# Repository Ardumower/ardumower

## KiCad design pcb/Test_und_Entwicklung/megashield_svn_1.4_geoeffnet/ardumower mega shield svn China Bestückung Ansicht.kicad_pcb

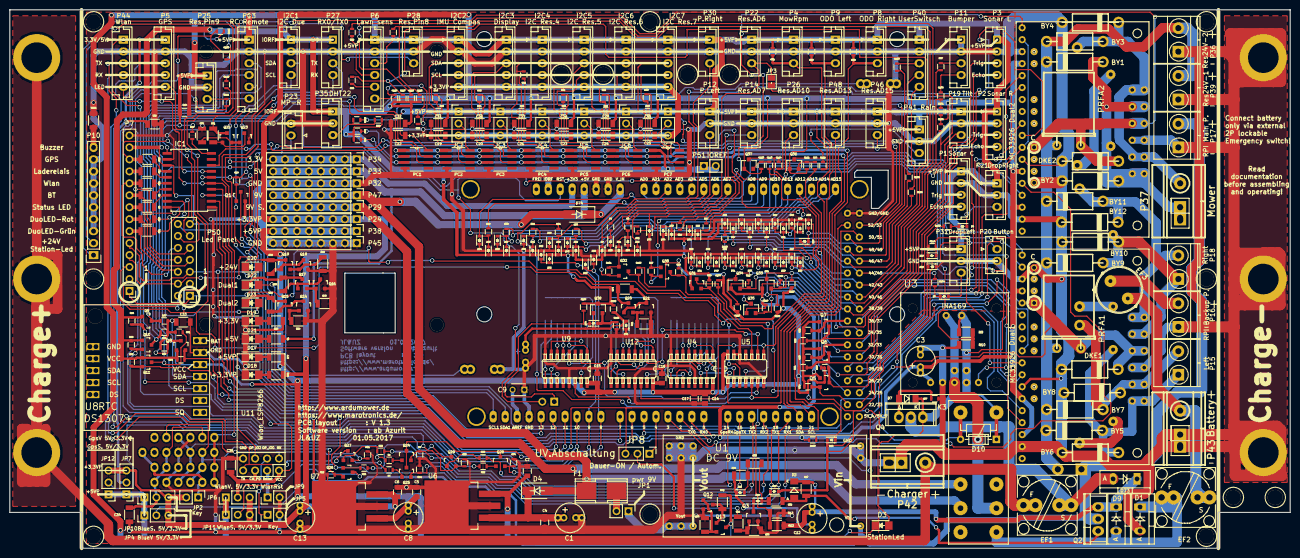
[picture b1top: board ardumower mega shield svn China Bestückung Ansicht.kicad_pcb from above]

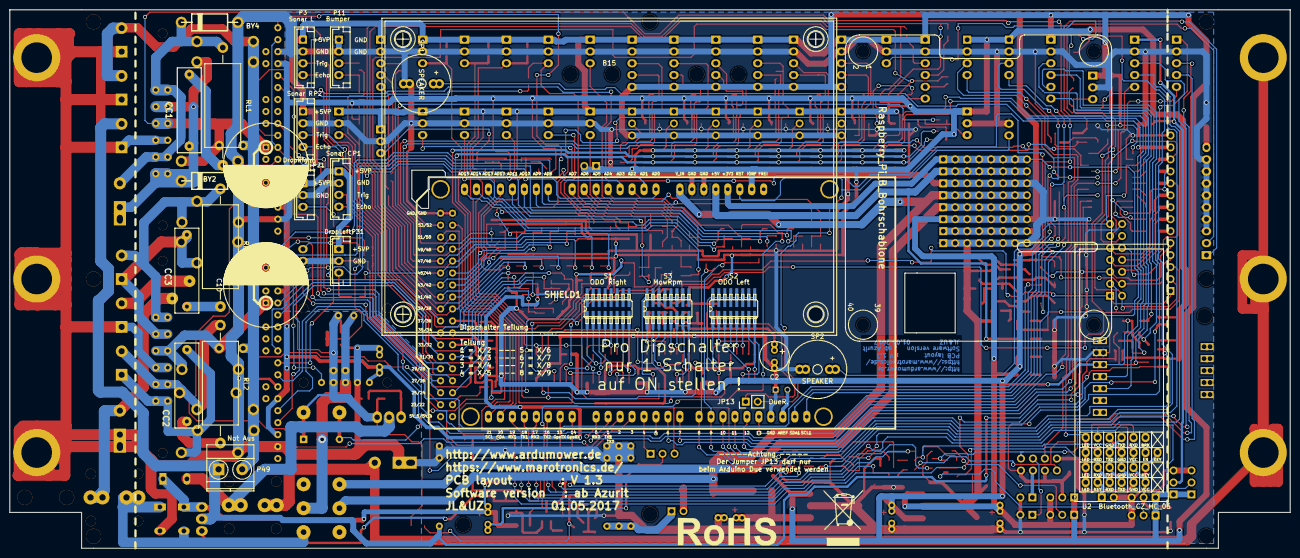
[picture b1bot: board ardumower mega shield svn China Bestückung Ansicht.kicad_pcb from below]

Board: 2 copper layers, 271.8 x 114.3 mm, 442 parts (21 on the bottom side), 281 nets.

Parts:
B1, B2, B3, B4, B5, B6, B7, B8, B17, B18, B19, B20, B21, B22: Bohrloch_3,2mm
B9, B10, B11, B12, B13, B14: Bohrloch_6,5mm
B15: BumperDuino_Bohrschablone
B16: Raspberry_Pi_B_Bohrschablone; Raspberry_Pi_B_Bohrschablone_Rueckseite
B23: Mülleimer; WEEE-Logo_8.4x12mm_SilkScreen
B24: Rohos; RoHS-Logo_6mm_SilkScreen
BY1, BY2, BY3, BY4, BY5, BY6, BY7, BY8, BY9, BY10, BY11, BY12: BY 500/1000; Diode_liegend_BY500_1000_RM15
C1, C8, C13: 22uF; Elko_vert_11.2x6.3mm_RM2.5_RM5.0
C2: 47uF; Elko_vert_11.2x6.3mm_RM2.5_RM5.0
C3: 10uF; Elko_vert_11.2x6.3mm_RM2.5_RM5.0
C4, C5, C6, C7, C14, C15, C16, C17, C18: 100nF; C_0805
C9: 100nF; C_Disc_D3_P2.5
C10, C11: 2200uF 63V; C_Radial_D18_L36_P7.5
C12: 22uF / 63V; Elko_vert_11.2x6.3mm_RM2.5_RM5.0
C19, C20, C21, C22, C23, C24, C25, C26, C27, C28, C29, C30, C31, C32, C33, C34, C35, C36: 100nF; C_1206
CC1, CC2, CC3: MP3-Y2 10N; Kondensator_cnp_18x5mm
D1, D9: MBR 1045; Diode_TO-220_Vertical
D2, D7: SMD ZF 15; MiniMELF_Standard
D3: StationLed; LED_1206
D4, D74: S 1G SMD; D_SMA_Standard
D5, D6, D8, D11, D12, D13, D14, D15, D16, D24, D25, D26, D27, D28, D29, D30, D31, D32, D33, D34, D35, D36, D37, D38, D39, D40, D41, D42, D43, D44, D45, D46, D47, D48, D49, D50, D51, D52, D53, D54, D55, D56, D57, D58, D59, D60, D61, D62, D63, D64, D65, D66, D67, D68, D69, D70, D71, D72, D75, D76: TSS0230LU; D_0603
D10: 1N4148; D_DO-35_SOD27_P7.62mm_Horizontal
D17: +5VP; LED_1206
D18: +3,3VP; LED_1206
D19: +3,3V; LED_1206
D20: +24V; LED_1206
D21: +5V; LED_1206
D22: Dual1; LED_1206
D23: Dual2; LED_1206
D73: MBR 1045; MBR1045
DKE1, DKE2: 15KE33CA; Diode_liegend_BY500_1000_RM15
Dual1, Dual2: MC33926; MC_33926_31polig_mit_Bohrloch_neue_Masse_mit_zweite_Lochrei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
EF1: F_5A; Fuseholder5x20_vert_closed_Bulgin_FX0456_und_TR15_Halter
EF2: F_10A; Fuseholder5x20_vert_closed_Bulgin_FX0456_und_TR15_Halter
EF3: 1A; Sicherungs_Sockel_für_TR5_TE5
F1: PTC; Fuse_SMD
I2C1: I2C Due; JST_EH_B04B-EH-A_04x2.50mm_Straight
I2C2: IMU Compas; JST_EH_B05B-EH-A_05x2.50mm_Straight
I2C3: Display; JST_EH_B05B-EH-A_05x2.50mm_Straight
I2C4: I2C Res.4; JST_EH_B05B-EH-A_05x2.50mm_Straight
I2C5: I2C Res.5; JST_EH_B05B-EH-A_05x2.50mm_Straight
I2C6: I2C Res.6; JST_EH_B05B-EH-A_05x2.50mm_Straight
I2C7: I2C Res.7; JST_EH_B05B-EH-A_05x2.50mm_Straight
IC1: UDN 2987 LWTR-6T; SOIC-20W_7.5x12.8mm_Pitch1.27mm
JC2, JC3, JC4, JC5, JC6, JC7: JUMPER3; Pin_Header_Straight_1x03_Pitch2.54mm
JP1: pwr 9V; Pin_Header_Straight_1x02_Pitch2.54mm
JP2, JP5: Key; Pin_Header_Straight_1x02_Pitch2.54mm
JP3: M1FB; SJ
JP4: BlueV 5V/3.3V; Pin_Header_Straight_1x03_Pitch2.54mm
JP6: WlanV. 5V/3.3V; Pin_Header_Straight_1x03_Pitch2.54mm
JP7: GpsV 5V/3.3V; Pin_Header_Straight_1x03_Pitch2.54mm
JP8: UV.Abschaltung; Pin_Header_Straight_1x03_Pitch2.54mm
JP9: WlanRst; Pin_Header_Straight_1x02_Pitch2.54mm
JP10: BlueS. 5V/3.3V; Pin_Header_Straight_1x03_Pitch2.54mm
JP11: WlanS. 5V/3.3V; Pin_Header_Straight_1x03_Pitch2.54mm
JP12: GpsS. 5V/3.3V; Pin_Header_Straight_1x03_Pitch2.54mm
JP13: DueR.; Pin_Header_Straight_1x02_Pitch2.54mm
K3: RELAY_2RT; Relais_DPDT_Schrack-RT2_RM5mm_3D_Kontaktbelegung_geändert_F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
P1: Sonar C; JST_EH_B04B-EH-A_04x2.50mm_Straight
P2: Sonar R; JST_EH_B04B-EH-A_04x2.50mm_Straight
P3: Sonar L; JST_EH_B04B-EH-A_04x2.50mm_Straight
P4: MowRpm; JST_EH_B03B-EH-A_03x2.50mm_Straight
P5: GPS; JST_EH_B05B-EH-A_05x2.50mm_Straight
P6: Lawn sens; JST_EH_B06B-EH-A_06x2.50mm_Straight
P7: Status LEDs; Socket_Strip_Straight_1x14_Pitch2.54mm
P8: ODO Right; JST_EH_B03B-EH-A_03x2.50mm_Straight
P9: ODO Left; JST_EH_B03B-EH-A_03x2.50mm_Straight
P10: Status LEDs GND; Socket_Strip_Straight_1x10_Led_Bargraph_Anzeige
P11: Bumper; JST_EH_B04B-EH-A_04x2.50mm_Straight
P12: P.Left; JST_EH_B03B-EH-A_03x2.50mm_Straight
P13: RC Remote; JST_EH_B06B-EH-A_06x2.50mm_Straight
P14: Res.AD7; JST_EH_B03B-EH-A_03x2.50mm_Straight
P15: Left; TerminalBlock_Pheonix_MKDS1.5-2pol
P16: RPI Backup P.; TerminalBlock_Pheonix_MKDS1.5-2pol
P17: RPI Main P.; TerminalBlock_Pheonix_MKDS1.5-2pol
P18: Right; TerminalBlock_Pheonix_MKDS1.5-2pol
P19: Tilt; JST_EH_B03B-EH-A_03x2.50mm_Straight
P20: Button; JST_EH_B02B-EH-A_02x2.50mm_Straight
P21: DropRight; JST_EH_B03B-EH-A_03x2.50mm_Straight
P22: Res.AD6; JST_EH_B03B-EH-A_03x2.50mm_Straight
P23: MP-R; JST_EH_B02B-EH-A_02x2.50mm_Straight
P24: +3.3VP; Pin_Header_Straight_1x08_Pitch2.54mm
P25: Res.Pin9; JST_EH_B03B-EH-A_03x2.50mm_Straight
P26: Res.AD10; JST_EH_B03B-EH-A_03x2.50mm_Straight
P27: RX0/TX0; JST_EH_B04B-EH-A_04x2.50mm_Straight
P28: Res.Pin8; JST_EH_B03B-EH-A_03x2.50mm_Straight
P29: 9V S.; Pin_Header_Straight_1x08_Pitch2.54mm
P30: P.Right; JST_EH_B03B-EH-A_03x2.50mm_Straight
P31: DropLeft; JST_EH_B03B-EH-A_03x2.50mm_Straight
P32, P45: GND; Pin_Header_Straight_1x08_Pitch2.54mm
P33: 5V; Pin_Header_Straight_1x08_Pitch2.54mm
P34: 3,3V; Pin_Header_Straight_1x08_Pitch2.54mm
P35: DHT22; JST_EH_B03B-EH-A_03x2.50mm_Straight
P36: Res24V-2; TerminalBlock_Pheonix_MKDS1.5-2pol
P37: Mower; Anschlussklemme_RM5,08-RM7,62
P38: +5VP; Pin_Header_Straight_1x08_Pitch2.54mm
P39: Res24V-1; TerminalBlock_Pheonix_MKDS1.5-2pol
P40: UserSwitsch; JST_EH_B05B-EH-A_05x2.50mm_Straight
P41: Rain; JST_EH_B03B-EH-A_03x2.50mm_Straight
P42: Charger; Anschlussklemme_RM5,08-RM7,62
P43: Battery; Anschlussklemme_RM5,08-RM7,62
P44: Wlan; JST_EH_B05B-EH-A_05x2.50mm_Straight
P46: Res.AD15; JST_EH_B03B-EH-A_03x2.50mm_Straight
P47: 9V; Pin_Header_Straight_1x08_Pitch2.54mm
P48: Res.AD13; JST_EH_B03B-EH-A_03x2.50mm_Straight
P49: Not Aus; TerminalBlock_Pheonix_MKDS1.5-2pol
P50: Led Panel; Pin_Header_Straight_2x07_Pitch2.54mm
P51: IOREF; Socket_Strip_Straight_1x02_Pitch2.54mm
PC1, PC2, PC3, PC4, PC5, PC6, PC7: PCA9517D; SOIC127P600X175-8N
PRFA1, PRFA2: PFRA 500; PRFA_500
Q1, Q24, Q25, Q26, Q27, Q28, Q29, Q38: BC847B; SOT-23
Q2, Q4: IRF9540N; TO-220
Q3, Q12, Q13, Q14, Q15, Q16, Q17, Q18, Q19, Q20, Q21, Q22, Q23: BC817; SOT-23
Q5, Q6, Q7, Q8, Q9, Q10, Q11, Q30, Q31, Q32, Q33, Q34, Q35, Q36, Q37: BSS138; SOT-23
R1, R2, R5, R17, R20, R21, R22, R25, R77, R134: 220R; R_1206
R3, R4, R26, R27, R29, R50, R54, R82, R83, R84, R85, R86, R87, R88, R89, R90, R103, R104, R105, R106, R107, R108, R109, R110, R111, R112: 300R; R_0603
R6, R7, R16, R28, R30, R31, R92, R93, R96: 4K7; R_0603
R8, R14, R15, R39, R42, R46, R49, R51, R52, R53, R55, R56, R58, R59, R60, R61, R62, R63, R64, R65, R66, R67, R68, R69, R70, R71, R91, R94, R95, R97, R98, R99, R100, R101, R102, R113, R114, R115, R116, R117, R118, R119, R120, R121, R122, R123, R124, R131, R132, R133, R137: 10K; R_0603
R9, R12: 100K 0,1%; R_1206
R10, R13: 10K 0,1%; R_1206
R11, R73, R79: 68R; R_1206
R18, R43: 2k2; R_0603
R19, R38, R72, R74, R76, R81: 8K2; R_1206
R23, R33, R78: 100R; R_1206
R24, R75, R80: 180R; R_1206
R32: 1K; R_1206
R34, R35: 10K; R_1206
R36: 30K; R_1206
R37: 100K; R_1206
R40, R41, R44, R45, R47, R48, R125, R126, R127, R128, R129, R130: XXXX; R_0603
R57: 100K; R_0603
R135: 56K; R_0603
R136: 1K; R_0603
RL1, RL2, RL3: 1,8R 2W METALL; Resistor_Horizontal_RM25mm-2W
S1: ODO Right; SW_DIP_x8_SMD
S2: ODO Left; SW_DIP_x8_SMD
S3: MowRpm; SW_DIP_x8_SMD
SHIELD1: ARDUINO_MEGA_SHIELD; ARDUINO_MEGA_SHIELD_DUO_3D
SP1, SP2: SPEAKER; Buzzer_12x9.5RM7.6_RM5.0
U1: DC 9V; DC_DC_DSN2596_mit_Bohrloch_doppelte_Lochreihe
U2: Bluetooth_CZ_HC_05; Bluetooth_Buchse_Platz_mit_Beschriftung_4_fach
U3: INA169
U4, U9, U12: 4017; 40xx-SO16
U5: 4081; 40xx-SO14
U6: LM2940CS-5.0; TO-263-3Lead
U7: LM3940IS-3.3; TO-263-3Lead
U8: DS1307+; Tiny_RTC_DS1307_geändert_mit_Bohrloch_4Lochreihen
U11: Wlan_ESP8266; Wlan_ESP8266_3D_mit_Pin_Beschreibung_ohne_Rahmen

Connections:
9Vgeschaltet: K3.3, P29.1, P29.2, P29.3, P29.4, P29.5, P29.6, P29.7, P29.8
+3.3VP: C6.1, C13.1, I2C2.5, I2C3.5, I2C4.5, I2C5.5, I2C6.5, I2C7.5, JC2.3, JC3.3, JC4.3, JC5.3, JC6.3, JC7.3, JP2.2, JP4.3, JP6.3, JP7.3, JP10.3, JP11.3, JP12.3, P24.1, P24.2, P24.3, P24.4, P24.5, P24.6, P24.7, P24.8, R78.1, U7.3
+3V3: P34.1, P34.2, P34.3, P34.4, P34.5, P34.6, P34.7, P34.8, R23.1, SHIELD1.3V3
+5V: P33.1, P33.2, P33.3, P33.4, P33.5, P33.6, P33.7, P33.8, R1.1, SHIELD1.5V
+5VP: C5.1, C7.1, C8.1, C14.1, C15.1, C16.1, C17.1, C18.1, C22.1, C33.1, I2C2.1, I2C3.1, I2C4.1, I2C5.1, I2C6.1, I2C7.1, IC1.11, JC2.1, JC3.1, JC4.1, JC5.1, JC6.1, JC7.1, JP4.1, JP6.1, JP7.1, JP10.1, JP11.1, JP12.1, P1.1, P2.1, P3.1, P4.1, P6.1, P8.1, P9.1, P12.1, P13.1, P14.1, P19.1, P21.1, P22.1, P25.1, P26.1, P28.1, P30.1, P31.1, P38.1, P38.2, P38.3, P38.4, P38.5, P38.6, P38.7, P38.8, P40.1, P41.1, P46.1, P48.1, PC1.8, R28.2, R30.2, R31.1, R43.1, R59.1, R61.1, R63.1, R65.1, R67.1, R69.1, R71.1, R77.1, R98.1, R100.1, R102.1, R116.1, R118.1, R120.1, R122.1, R124.1, U4.16, U5.14, U6.3, U7.1, U8.3, U9.16, U12.16
+9V: D4.2, D74.2, F1.2, K3.5, P47.1, P47.2, P47.3, P47.4, P47.5, P47.6, P47.7, P47.8
+24V: D20.2, P7.5, P17.2, P49.1, P50.5, Q2.2, U1.3
/Anschlußstecker/LShifter1/5V_IN: P1.4, Q5.3, R59.2
/Anschlußstecker/LShifter2/5V_IN: P2.4, Q6.3, R61.2
/Anschlußstecker/LShifter3/5V_IN: P3.4, Q7.3, R63.2
/Anschlußstecker/LShifter4/5V_IN: P13.3, Q8.3, R65.2
/Anschlußstecker/LShifter5/5V_IN: P13.4, Q9.3, R67.2
/Anschlußstecker/LShifter6/5V_IN: P13.5, Q10.3, R69.2
/Anschlußstecker/LShifter7/5V_IN: P13.6, Q11.3, R71.2
/Anschlußstecker/LShifter8/5V_IN: Q30.3, R98.2, U5.10
/Anschlußstecker/LShifter9/5V_IN: Q31.3, R100.2, U5.4
/Anschlußstecker/LShifter10/5V_IN: Q32.3, R102.2, U5.3
/Anschlußstecker/LShifter11/5V_IN: P3.3, Q33.3, R116.2
/Anschlußstecker/LShifter12/5V_IN: P2.3, Q34.3, R118.2
/Anschlußstecker/LShifter13/5V_IN: P1.3, Q35.3, R120.2
/Anschlußstecker/LShifter14/5V_IN: P41.3, Q36.3, R122.2
/Anschlußstecker/LShifter15/5V_IN: P19.3, Q37.3, R124.2
/Anschlußstecker/OdoTeiler/Eingang1: P8.3, R28.1, U4.14, U5.1
/Anschlußstecker/OdoTeiler/Eingang2: P9.3, R30.1, U5.5, U9.14
/Anschlußstecker/OdoTeiler/Eingang3: P4.3, R31.2, U5.8, U12.14
/Motortreiber/+24V: BY1.1, BY3.1, BY5.1, BY7.1, BY9.1, BY11.1, P36.2, P39.2, P49.2, PRFA1.1, PRFA2.1
/Motortreiber/MotorLinks/MotorIN1: BY5.2, BY6.1, CC2.1, Dual1.19, P15.1
/Motortreiber/MotorLinks/MotorIN2: BY7.2, BY8.1, Dual1.20, P15.2, RL2.2
/Motortreiber/MotorRechts/MotorIN1: BY9.2, BY10.1, CC3.1, Dual1.23, P18.1
/Motortreiber/MotorRechts/MotorIN2: BY11.2, BY12.1, Dual1.24, P18.2, RL3.2
/Motortreiber/MähmotorSchutz/MotorIN1: BY1.2, BY2.1, CC1.1, Dual2.19, Dual2.23, P37.1
/Motortreiber/MähmotorSchutz/MotorIN2: BY3.2, BY4.1, Dual2.20, Dual2.24, P37.2, RL1.2
/USpannungAB/Batterieeingang 24V: C12.1, D2.1, D9.1, D73.1, Q2.3, R12.1, R37.1
/VerpolungsschutzLade./Eingang: D73.2, EF1.2, Q4.2
Charg_Pin_+: B9.1, B10.1, B11.1, EF1.1, P42.2
DHT22: P35.3, R39.2, R109.1
DropLeft: D5.1, P31.3
DropRight: D6.1, P21.3
Dual1: C10.1, D22.2, DKE1.1, Dual1.22, PRFA1.2
Dual2: C11.1, D23.2, DKE2.1, Dual2.22, PRFA2.2
DuoLED-Rot: IC1.2, SHIELD1.7
DuoLED_Grün: IC1.1, SHIELD1.6
GND: B12.1, B13.1, B14.1, BY2.2, BY4.2, BY6.2, BY8.2, BY10.2, BY12.2, C1.2, C2.2, C3.2, C4.2, C5.2, C6.2, C7.2, C8.2, C9.1, C10.2, C11.2, C13.2, C14.2, C15.2, C16.2, C17.2, C18.2, C19.2, C20.2, C21.2, C22.2, C23.2, C24.2, C25.2, C26.2, C27.2, C28.2, C29.2, C30.2, C31.2, C32.2, C33.2, C34.2, C35.2, C36.2, D1.2, D16.2, D17.1, D18.1, D19.1, D21.1, D24.2, D25.2, D27.2, D30.2, D34.2, D35.2, D36.2, D38.2, D40.2, D42.2, D44.2, D46.2, D48.2, D50.2, D52.2, D54.2, D56.2, D58.2, D60.2, D62.2, D64.2, D66.2, D68.2, D70.2, D72.2, D75.2, DKE1.2, DKE2.2, Dual1.2, Dual1.7, Dual1.16, Dual1.21, Dual2.2, Dual2.7, Dual2.16, Dual2.21, I2C1.2, I2C2.2, I2C3.2, I2C4.2, I2C5.2, I2C6.2, I2C7.2, IC1.12, JP5.2, JP9.2, P1.2, P2.2, P3.2, P4.2, P5.2, P6.2, P7.14, P8.2, P9.2, P10.3, P10.4, P10.5, P10.6, P10.7, P10.8, P10.9, P11.1, P11.2, P12.2, P13.2, P14.2, P16.1, P17.1, P19.2, P20.2, P21.2, P22.2, P23.2, P25.2, P26.2, P27.2, P28.2, P30.2, P31.2, P32.1, P32.2, P32.3, P32.4, P32.5, P32.6, P32.7, P32.8, P35.2, P36.1, P39.1, P40.2, P41.2, P42.1, P43.1, P44.2, P45.1, P45.2, P45.3, P45.4, P45.5, P45.6, P45.7, P45.8, P46.2, P48.2, P50.14, PC1.4, PC2.4, PC3.4, PC4.4, PC5.4, PC6.4, PC7.4, Q1.2, Q3.2, Q12.2, Q14.2, Q16.2, Q18.2, Q21.2, Q23.2, R8.2, R10.2, R11.2, R13.2, R14.2, R15.2, R24.2, R35.2, R57.2, R73.2, R75.2, R79.2, R80.2, R91.2, R94.2, R95.2, R134.2, R136.2, SHIELD1.GND1, SHIELD1.GND2, SHIELD1.GND3, SHIELD1.GND4, SHIELD1.GND5, SP1.1, SP2.1, U1.1, U1.4, U2.GND, U3.2, U4.8, U4.13, U5.7, U5.12, U5.13, U6.2, U6.4, U7.2, U7.4, U8.2, U9.8, U9.13, U11.GND, U12.8, U12.13
GPS-LED: IC1.7, P5.5
GPS_RX: Q28.2, R94.1, SHIELD1.14
GPS_TX: R96.2, SHIELD1.15
IOREF: C3.1, C26.1, C27.1, C28.1, C29.1, C30.1, C31.1, C32.1, D8.1, D11.1, D26.1, D28.1, D29.1, D31.1, D32.1, D33.1, D37.1, D39.1, D41.1, D43.1, D45.1, D47.1, D49.1, D51.1, D53.1, D55.1, D57.1, D59.1, D61.1, D63.1, D65.1, D67.1, D69.1, D71.1, Dual1.3, Dual1.6, Dual1.15, Dual2.3, Dual2.6, Dual2.15, I2C1.1, JP8.3, P27.1, P35.1, P51.1, P51.2, PC1.1, PC2.1, PC3.1, PC4.1, PC5.1, PC6.1, PC7.1, Q5.1, Q6.1, Q7.1, Q8.1, Q9.1, Q10.1, Q11.1, Q24.3, Q25.3, Q28.3, Q30.1, Q31.1, Q32.1, Q33.1, Q34.1, Q35.1, Q36.1, Q37.1, Q38.3, R39.1, R47.1, R48.1, R58.1, R60.1, R62.1, R64.1, R66.1, R68.1, R70.1, R97.1, R99.1, R101.1, R113.2, R114.2, R115.1, R117.1, R119.1, R121.1, R123.1, R125.2, R126.2, R127.2, R128.2, R129.2, R130.2, R131.2, R132.2, R133.2, R135.1, R137.2, SHIELD1.IORE, U3.1
Led-BT: IC1.4, U2.LED
Led-Status: IC1.3, SHIELD1.13
Led-Wlan: IC1.5, P44.5, U11.GP_2
unnamed: C1.1, C4.1, D4.1, U6.1
unnamed: C2.1, D75.1, Q38.1, R135.2
unnamed: C9.2, SHIELD1.AREF
unnamed: C12.2, D12.2, R34.1
unnamed: C19.1, JC2.2, PC2.8, R40.1, R44.1
unnamed: C20.1, JC3.2, PC3.8, R41.1, R45.1
unnamed: C21.1, JC4.2, PC4.8, R42.1, R46.1
unnamed: C23.1, JC5.2, PC5.8, R51.1, R55.1
unnamed: C24.1, JC6.2, PC6.8, R52.1, R56.1
unnamed: C25.1, JC7.2, PC7.8, R49.1, R53.1
unnamed: C34.1, JP4.2, U2.VCC
unnamed: C35.1, JP6.2, P44.1, U11.CH_P, U11.VCC
unnamed: C36.1, JP7.2, P5.1
unnamed: CC1.2, RL1.1
unnamed: CC2.2, RL2.1
unnamed: CC3.2, RL3.1
unnamed: D1.1, D9.2, EF2.1, K3.16
unnamed: D2.2, Q2.1, R32.2, R37.2
unnamed: D3.1, Q13.3, R72.1
unnamed: D5.2, R104.1
unnamed: D6.2, R103.1
unnamed: D7.2, Q4.1, R57.1
unnamed: D10.2, K3.9, Q1.3
unnamed: D11.2, D24.1, R3.2, SHIELD1.AD5
unnamed: D12.1, R33.1, R34.2
unnamed: D13.2, D15.2, R32.1, R33.2
unnamed: D15.1, Q3.3
unnamed: D8.2, D16.1, R4.2, SHIELD1.AD4
unnamed: D17.2, R77.2
unnamed: D18.2, R78.2
unnamed: D19.2, R23.2
unnamed: D20.1, Q19.3, R76.1
unnamed: D21.2, R1.2
unnamed: D22.1, Q17.3, R38.1
unnamed: D23.1, Q15.3, R19.1
unnamed: D25.1, D26.2, R103.2, R114.1, SHIELD1.23
unnamed: D27.1, D28.2, R110.2, SHIELD1.35
unnamed: D29.2, D30.1, R87.2, R132.1, SHIELD1.38
unnamed: D31.2, D34.1, R105.2, R131.1, SHIELD1.39
unnamed: D32.2, D35.1, R111.2, R129.1, SHIELD1.9
unnamed: D33.2, D36.1, R112.2, R130.1, SHIELD1.8
unnamed: D37.2, D38.1, R29.2, R126.1, SHIELD1.40
unnamed: D39.2, D40.1, R54.2, R125.1, SHIELD1.41
unnamed: D41.2, D42.1, R83.2, R128.1, SHIELD1.42
unnamed: D43.2, D44.1, R85.2, R127.1, SHIELD1.43
unnamed: D45.2, D46.1, R86.2, SHIELD1.44
unnamed: D47.2, D48.1, R104.2, R113.1, SHIELD1.45
unnamed: D49.2, D50.1, R108.2, SHIELD1.47
unnamed: D51.2, D52.1, R106.2, SHIELD1.46
unnamed: D53.2, D54.1, R26.2, SHIELD1.AD7
unnamed: D55.2, D56.1, R82.2, SHIELD1.AD6
unnamed: D57.2, D58.1, R109.2, SHIELD1.49
unnamed: D59.2, D60.1, R84.2, SHIELD1.AD2
unnamed: D61.2, D62.1, R107.2, SHIELD1.48
unnamed: D63.2, D64.1, R90.2, SHIELD1.AD8
unnamed: D65.2, D66.1, R27.2, SHIELD1.AD15
unnamed: D67.2, D68.1, R89.2, SHIELD1.AD9
unnamed: D69.2, D70.1, R50.2, SHIELD1.AD13
unnamed: D71.2, D72.1, R88.2, SHIELD1.AD10
unnamed: D74.1, SHIELD1.V_IN
unnamed: D76.1, Q38.2, R136.1
unnamed: D76.2, JP13.1, R137.1
unnamed: Dual2.9, JP3.2
unnamed: EF2.2, EF3.1, P43.2
unnamed: EF3.2, P16.2
unnamed: F1.1, JP1.2
unnamed: IC1.10, R43.2
unnamed: IC1.13, P7.13, P50.13, SP1.2, SP2.2
unnamed: IC1.14, R25.1
unnamed: IC1.15, R17.1
unnamed: IC1.16, R22.1
unnamed: IC1.17, R2.1
unnamed: IC1.18, R5.1
unnamed: IC1.19, R20.1
unnamed: IC1.20, R21.1
unnamed: JP1.1, U1.2
unnamed: JP2.1, U2.Key
unnamed: JP5.1, U11.GP_0
unnamed: JP8.2, R36.2
unnamed: JP9.1, U11.Rese
unnamed: JP10.2, Q26.3
unnamed: JP11.2, Q27.3
unnamed: JP12.2, Q29.3
unnamed: K3.12, U3.5
unnamed: P5.3, R93.2
unnamed: P5.4, Q29.2, R95.1
unnamed: P7.2, P10.1, P50.2, Q22.3, R81.1
unnamed: P7.3, P10.2, P50.3, Q20.3, R74.1
unnamed: P10.10, R134.1
unnamed: P44.3, R7.2, U11.TX
unnamed: P44.4, Q27.2, R91.1, U11.RX
unnamed: P7.6, P50.6, R21.2
unnamed: P7.7, P50.7, R20.2
unnamed: P7.8, P50.8, R5.2
unnamed: P7.9, P50.9, R2.2
unnamed: P7.10, P50.10, R22.2
unnamed: P7.11, P50.11, R17.2
unnamed: P7.12, P50.12, R25.2
unnamed: Q1.1, R18.2
unnamed: Q3.1, R35.1, R36.1
unnamed: Q12.1, Q13.2, R73.1
unnamed: Q12.3, Q13.1, R72.2
unnamed: Q14.1, Q15.2, R24.1
unnamed: Q14.3, Q15.1, R19.2
unnamed: Q16.1, Q17.2, R75.1
unnamed: Q16.3, Q17.1, R38.2
unnamed: Q18.1, Q19.2, R80.1
unnamed: Q18.3, Q19.1, R76.2
unnamed: Q20.1, Q21.3, R74.2
unnamed: Q20.2, Q21.1, R11.1
unnamed: Q22.1, Q23.3, R81.2
unnamed: Q22.2, Q23.1, R79.1
unnamed: Q24.1, R6.1
unnamed: Q25.1, R7.1
unnamed: Q26.1, R16.1
unnamed: Q26.2, R15.1, U2.RXD
unnamed: Q27.1, R92.1
unnamed: Q28.1, R93.1
unnamed: Q29.1, R96.1
unnamed: R6.2, U2.TXD
unnamed: S1.1, U4.4
unnamed: S1.2, U4.7
unnamed: S1.3, U4.10
unnamed: S1.4, U4.1
unnamed: S1.5, U4.5
unnamed: S1.6, U4.6
unnamed: S1.7, U4.9
unnamed: S1.8, U4.11
unnamed: S1.9, S1.10, S1.11, S1.12, S1.13, S1.14, S1.15, S1.16, U4.15
unnamed: S2.1, U9.4
unnamed: S2.2, U9.7
unnamed: S2.3, U9.10
unnamed: S2.4, U9.1
unnamed: S2.5, U9.5
unnamed: S2.6, U9.6
unnamed: S2.7, U9.9
unnamed: S2.8, U9.11
unnamed: S2.9, S2.10, S2.11, S2.12, S2.13, S2.14, S2.15, S2.16, U9.15
unnamed: S3.1, U12.4
unnamed: S3.2, U12.7
unnamed: S3.3, U12.10
unnamed: S3.4, U12.1
unnamed: S3.5, U12.5
unnamed: S3.6, U12.6
unnamed: S3.7, U12.9
unnamed: S3.8, U12.11
unnamed: S3.9, S3.10, S3.11, S3.12, S3.13, S3.14, S3.15, S3.16, U12.15
unnamed: U4.2, U5.2
unnamed: U5.6, U9.2
unnamed: U5.9, U12.2
RX0: P27.3, SHIELD1.0
RX1: Q25.2, R14.1, SHIELD1.19
RX2: Q24.2, R8.1, SHIELD1.17
RelaisAbschaltung: JP8.1, SHIELD1.4
ReserveAD6: JP3.1, P22.3, R82.1
ReserveAD7: P14.3, R26.1
ReserveAD10: P26.3, R88.1
ReservePin8: P28.3, R112.1
ReservePin9: P25.3, R111.1
Reset: JP13.2, P23.1, SHIELD1.RST
Resv.PinAD13: P48.3, R50.1
Resv.PinAD15: P46.3, R27.1
SCL: PC1.2, PC2.2, PC3.2, PC4.2, PC5.2, PC6.2, PC7.2, R48.2, SHIELD1.21
SCL1: PC1.7, U8.5
SCL2: I2C2.4, PC2.7, R44.2
SCL3: I2C3.4, PC3.7, R45.2
SCL4: I2C4.4, PC4.7, R46.2
SCL5: I2C5.4, PC5.7, R51.2
SCL6: I2C6.4, PC6.7, R52.2
SCL7: I2C7.4, PC7.7, R49.2
SCL22: I2C1.4, SHIELD1.SCL1
SDA: PC1.3, PC2.3, PC3.3, PC4.3, PC5.3, PC6.3, PC7.3, R47.2, SHIELD1.20
SDA1: PC1.6, U8.4
SDA2: I2C2.3, PC2.6, R40.2
SDA3: I2C3.3, PC3.6, R41.2
SDA4: I2C4.3, PC4.6, R42.2
SDA5: I2C5.3, PC5.6, R55.2
SDA6: I2C6.3, PC6.6, R56.2
SDA7: I2C7.3, PC7.6, R53.2
SDA22: I2C1.3, SHIELD1.SDA1
StationLed: D3.2, D7.1, D10.1, K3.8, P7.4, P50.4, Q4.3, R9.1, U3.4
TX0: P27.4, SHIELD1.1
TX1: R92.2, SHIELD1.18
TX2: R16.2, SHIELD1.16
Taster: D13.1, D14.1, P7.1, P20.1, P50.1
pinBatteryVoltage: R12.2, R13.1, R84.1
pinBumperLeft: P11.4, R105.1
pinBumperRight: P11.3, R87.1
pinButton: D14.2, R133.1, SHIELD1.51
pinBuzzer: IC1.8, SHIELD1.53
pinChargeCurrent: R90.1, U3.3
pinChargeVoltage: R9.2, R10.1, R89.1
pinChargingEnable: IC1.6, R18.1, SHIELD1.50
pinLawnBackRecv: P6.6, R83.1
pinLawnBackSend: P6.5, R85.1
pinLawnFrontRecv: P6.4, R29.1
pinLawnFrontSend: P6.3, R54.1
pinMotorEnable: Dual1.10, SHIELD1.37
pinMotorLeftDir: Dual1.4, SHIELD1.31
pinMotorLeftFault: Dual1.8, SHIELD1.25
pinMotorLeftPWM: Dual1.5, SHIELD1.5
pinMotorLeftSense: Dual1.9, SHIELD1.AD1
pinMotorMowDir: Dual2.4, Dual2.13, SHIELD1.29
pinMotorMowEnable: Dual2.10, SHIELD1.28
pinMotorMowFault: Dual2.8, Dual2.17, SHIELD1.26
pinMotorMowPWM: Dual2.5, Dual2.14, SHIELD1.2
pinMotorMowRpm_neu: Q30.2, R97.2, SHIELD1.AD11
pinMotorMowSense: Dual2.18, SHIELD1.AD3
pinMotorRightDir: Dual1.13, SHIELD1.33
pinMotorRightFault: Dual1.17, SHIELD1.27
pinMotorRightPWM: Dual1.14, SHIELD1.3
pinMotorRightSense: Dual1.18, SHIELD1.AD0
pinOdometryLeft: Q31.2, R99.2, SHIELD1.AD12
pinOdometryRight: Q32.2, R101.2, SHIELD1.AD14
pinPerimeterLeft: P12.3, R3.1
pinPerimeterRight: P30.3, R4.1
pinRain: Q36.2, R86.1, R121.2
pinRemoteMow: Q8.2, R64.2, SHIELD1.12
pinRemoteSpeed: Q10.2, R68.2, SHIELD1.10
pinRemoteSteer: Q9.2, R66.2, SHIELD1.11
pinRemoteSwitch: Q11.2, R70.2, SHIELD1.52
pinSonarCenterEcho: Q5.2, R58.2, SHIELD1.22
pinSonarCenterTrigger: Q35.2, R119.2, SHIELD1.24
pinSonarLeftEcho: Q7.2, R62.2, SHIELD1.36
pinSonarLeftTrigger: Q33.2, R115.2, SHIELD1.34
pinSonarRightEcho: Q6.2, R60.2, SHIELD1.32
pinSonarRightTrigger: Q34.2, R117.2, SHIELD1.30
pinTilt: Q37.2, R110.1, R123.2
pinUserSwitch1: P40.5, R106.1
pinUserSwitch2: P40.4, R108.1
pinUserSwitch3: P40.3, R107.1

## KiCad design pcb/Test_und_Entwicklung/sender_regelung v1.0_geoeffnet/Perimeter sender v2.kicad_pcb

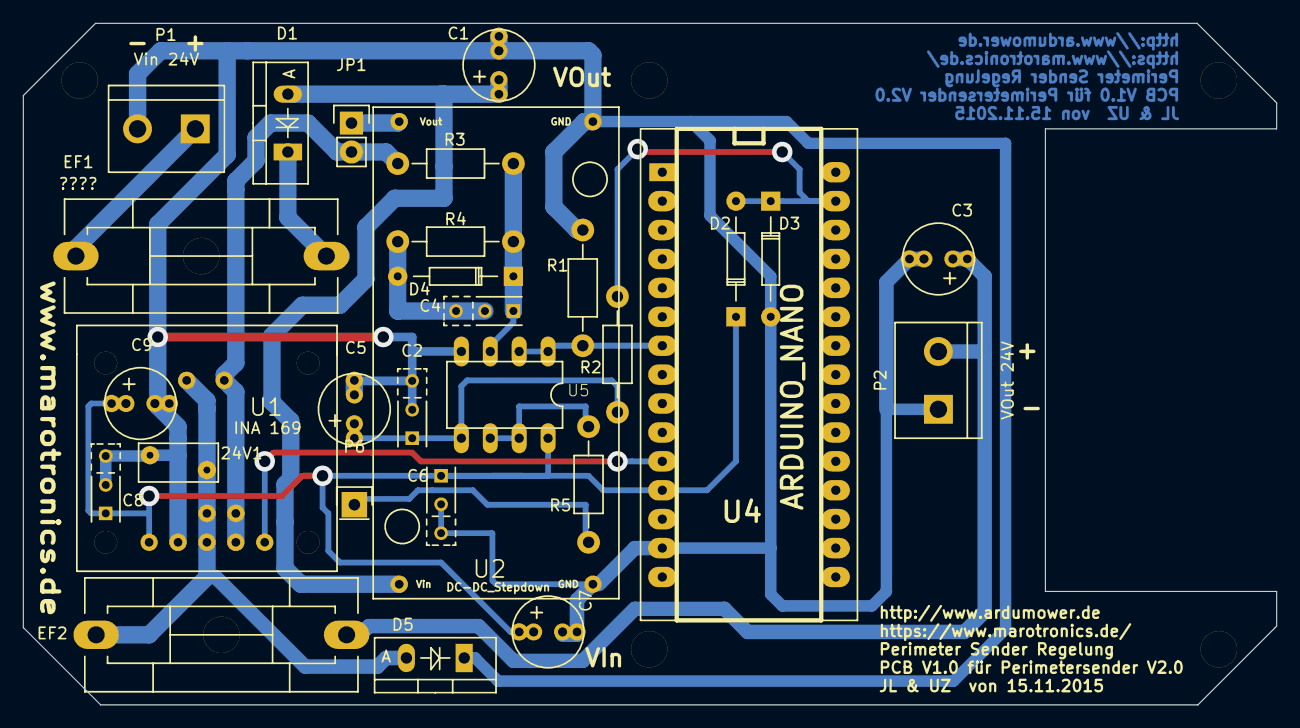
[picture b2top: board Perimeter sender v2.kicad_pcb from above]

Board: 2 copper layers, 110.1 x 59.9 mm, 35 parts (0 on the bottom side), 17 nets.

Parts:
24V1: VR; RV_Disc_D7_W3.4_P5
B1, B2, B3, B5, B6: Bohrloch_3,2mm
C1, C3: 220uF/63V; Elko_vert_11.2x6.3mm_RM2.5_RM5.0
C2: 220nF; C_Rect_L4_W2.5_P2.5_P5.0
C4: 47pP; C_Rect_L4_W2.5_P2.5_P5.0
C5: 47uF/16V; Elko_vert_11.2x6.3mm_RM2.5_RM5.0
C6, C8: 100nF; C_Rect_L4_W2.5_P2.5_P5.0
C7, C9: 10uF/16V; Elko_vert_11.2x6.3mm_RM2.5_RM5.0
D1, D5: MBR 1045; Diode_TO-220_Vertical
D2, D3: 1N4148; Diode_DO-35_SOD27_Horizontal_RM10
D4: ZPD5,1V; Diode_DO-35_SOD27_Horizontal_RM10
EF1, EF2: ????; Fuseholder_Reichelt_PL112000
JP1: PWR; Pin_Header_Straight_1x02
P1: Vin 24V; Anschlussklemme_2P_RM5,08
P2: VOut 24V; Anschlussklemme_2P_RM5,08
P6: CONN_01X01; Pin_Header_Straight_1x01
R1, R4: 10K/1%; Resistor_Horizontal_RM10mm
R2: 47K; Resistor_Horizontal_RM10mm
R3: 100K/1%; Resistor_Horizontal_RM10mm
R5: 1K; Resistor_Horizontal_RM10mm
U1: INA 169; INA169
U2: DC-DC_Stepdown; DC_DC_DSN2596_mit_Bohrloch
U4: ARDUINO_NANO; arduino_nano
U5: OPA2340PA; 40xx-DIL08

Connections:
+5V: C6.1, C7.1, C8.1, C9.1, D2.1, U1.1, U4.5V, U5.8
A3: R1.1, U4.A3, U5.1, U5.2
A7: U1.3, U4.A7
D11: D2.2, D3.1, R2.2, U4.D11
DC_Wandler_Pin_4: P6.1, R5.1
GND: 24V1.2, C1.2, C2.2, C3.2, C5.2, C6.2, C7.2, C8.2, C9.2, D3.2, D5.1, P1.2, P2.1, R1.2, U1.2, U2.1, U2.4, U4.GND1, U5.4
unnamed: 24V1.1, D5.2, EF2.2, U1.5
unnamed: C1.1, D1.2, U2.3
unnamed: C2.1, C5.1, R2.1, U5.5
unnamed: C3.1, EF2.1, P2.2
unnamed: C4.1, D4.1, R3.2, R4.1, U5.3
unnamed: C4.2, D4.2, R4.2
unnamed: D1.1, EF1.1
unnamed: EF1.2, P1.1
unnamed: JP1.1, U2.2
unnamed: JP1.2, R3.1, U1.4
unnamed: R5.2, U5.6, U5.7

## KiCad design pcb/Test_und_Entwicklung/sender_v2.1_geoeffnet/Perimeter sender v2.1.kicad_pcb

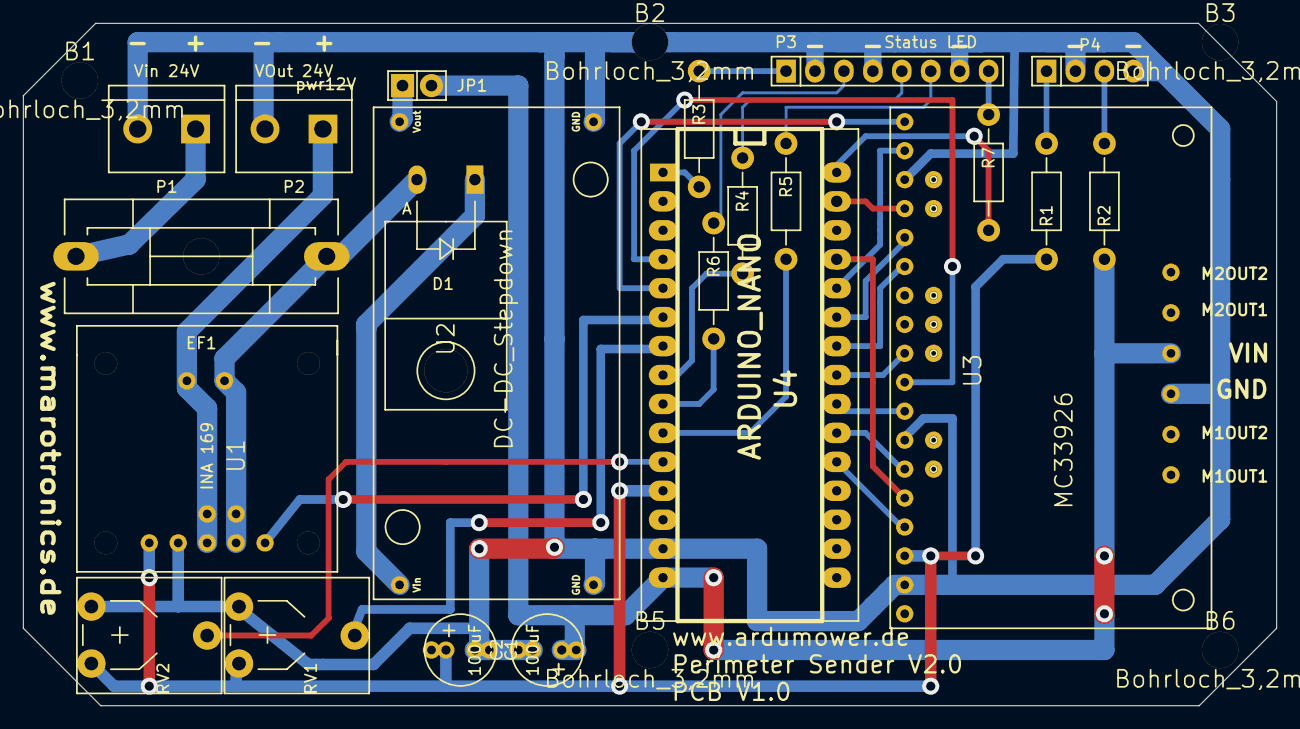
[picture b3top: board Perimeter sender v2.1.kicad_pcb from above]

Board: 2 copper layers, 110.0 x 59.9 mm, 27 parts (0 on the bottom side), 34 nets.

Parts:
B1, B2, B3, B5, B6: Bohrloch_3,2mm
C1, C2: 100uF; Elko_vert_11.2x6.3mm_RM2.5_RM5.0
D1: MBR 1045; MBR1045_Horizontal
EF1: F_5A; Fuseholder_Reichelt_PL112000
JP1: pwr12V; Pin_Header_Straight_1x02
P1: Vin 24V; Anschlussklemme_2P_RM5,08
P2: VOut 24V; Anschlussklemme_2P_RM5,08
P3: Status LED; Pin_Header_Straight_1x08
P4: Power LED; Pin_Header_Straight_1x04
R1, R3, R4, R5, R6, R7: 220; Resistor_Horizontal_RM10mm
R2: 560; Resistor_Horizontal_RM10mm
RV1, RV2: 47K; Potentiometer_VishaySpectrol-Econtrim-Type36T_3D-angepasst_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
U1: INA 169; INA169
U2: DC-DC_Stepdown; DC_DC_DSN2596_mit_Bohrloch
U3: MC33926; MC_33926_31polig_mit_Bohrloch_neue_Masse
U4: ARDUINO_NANO; arduino_nano

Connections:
+5V: C1.1, R1.1, RV1.3, RV2.3, U1.1, U3.3, U4.5V
+12V: C2.1, JP1.2, R2.1, U3.22, U4.VIN
EN: U3.10, U4.D5
GND: C1.2, C2.2, P1.2, P2.2, P3.2, P3.4, P3.7, P4.2, P4.4, RV1.1, RV2.1, U1.2, U2.1, U2.4, U3.2, U3.7, U3.16, U3.21, U4.GND1
INA169: U1.3, U4.A2
LED_5V: P4.1, R1.2
LED_12V: P4.3, R2.2
M1FB: U3.9, U4.A0
M1IN1: U3.5, U4.D9
M1IN2: U3.4, U4.D2
M1_DuoLED_Schleife1_Grün: P3.8, R7.1
M1_DuoLED_Schleife1_Rot: P3.6, R5.1
M1nD2 pwm: U3.6, U4.D3
M1nSF: U3.8, U4.D4
M2FB: U3.18, U4.A1
M2IN1: U3.14, U4.D7
M2IN2: U3.13, U4.D6
M2_DuoLED_Schleife2_Grün: P3.3, R6.1
M2_DuoLED_Schleife2_Rot: P3.5, R4.1
M2nD2 pwm: U3.15, U4.D11
M2nSF: U3.17, U4.D8
Mover_in_Ladestation: P3.1, R3.1
unnamed: D1.1, EF1.1, U1.4
unnamed: D1.2, U2.3
unnamed: EF1.2, P1.1
unnamed: JP1.1, U2.2
unnamed: P2.1, U1.5
unnamed: R3.2, U4.D13
unnamed: R4.2, U4.A4
unnamed: R5.2, U4.A6
unnamed: R6.2, U4.A5
unnamed: R7.2, U4.D12
POTI1: RV1.2, U4.A3
POTI2: RV2.2, U4.A7

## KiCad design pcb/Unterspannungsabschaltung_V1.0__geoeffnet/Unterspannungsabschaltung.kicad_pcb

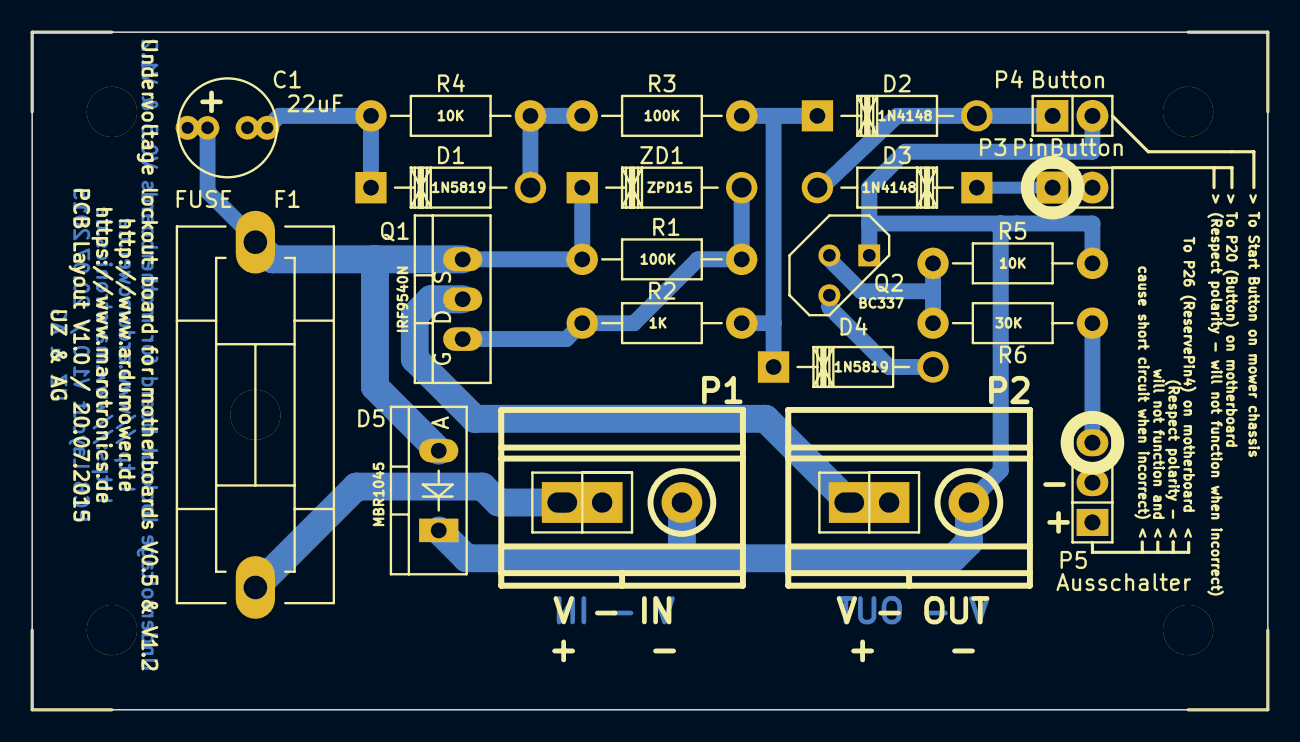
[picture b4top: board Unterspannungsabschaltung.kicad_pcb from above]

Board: 2 copper layers, 78.7 x 43.2 mm, 25 parts (0 on the bottom side), 13 nets.

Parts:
B1, B2, B3, B4: Bohrloch; Bohrloch_3,2mm
C1: 22uF; Elko_vert_11.2x6.3mm_RM2.5_RM5.0
D1, D4: 1N5819; Diode_ligend_RM10
D2, D3: 1N4148; Diode_ligend_RM10
D5: MBR1045
F1: FUSE; Fuseholder_Reichelt_PL112000
P1: Batterieeingang 24V; Anschlussklemme_RM5,08-RM7,62
P2: Batterieausgang 24V; Anschlussklemme_RM5,08-RM7,62
P3: PinButton; Pin_Header_Straight_1x02
P4: Button; Pin_Header_Straight_1x02
P5: Ausschalter; Pin_Header_Straight_1x03
Q1: IRF9540N; TO-220_FET-GDS_Vertical
Q2: BC337; TO92-EBC
R1, R3: 100K; Resistor_Horizontal_RM10mm
R2: 1K; Resistor_Horizontal_RM10mm
R4, R5: 10K; Resistor_Horizontal_RM10mm
R6: 30K; Resistor_Horizontal_RM10mm
ZD1: ZPD15; Diode_ligend_RM10

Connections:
GND: D5.2, P1.2, P2.2, P4.2, Q2.E, R5.2
unnamed: C1.1, D5.1, F1.2, Q1.S, R1.1, ZD1.C
unnamed: C1.2, D1.2, R4.1
unnamed: D1.1, R3.1, R4.2
unnamed: D2.1, D3.1, P4.1
unnamed: D2.2, D4.2, R2.1, R3.2
unnamed: D3.2, P3.1
unnamed: D4.1, Q2.C
unnamed: F1.1, P1.1
unnamed: P2.1, Q1.D
unnamed: P5.3, R6.2
unnamed: Q1.G, R1.2, R2.2, ZD1.A
unnamed: Q2.B, R5.1, R6.1

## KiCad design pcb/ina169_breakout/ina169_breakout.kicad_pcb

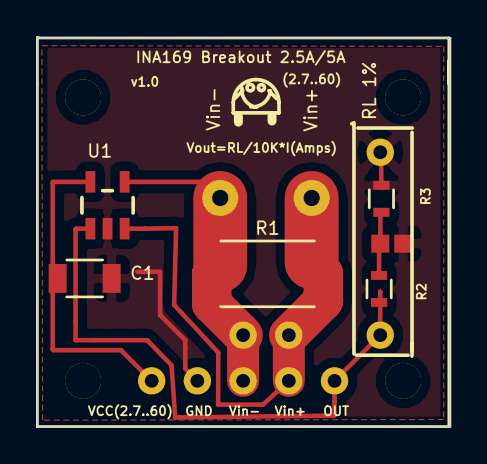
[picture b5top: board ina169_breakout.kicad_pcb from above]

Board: 2 copper layers, 23.0 x 21.7 mm, 6 parts (0 on the bottom side), 6 nets.

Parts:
C1: 0.1uF; C_1206
J1: INA169 Breakout 2.5A/5A; ina169_breakout_footprint
R1: 0.1 1% 2W; R_2512
R2, R3: 10K 1%; R_0603
U1: INA169_IC; ina169_ic_sot23-5

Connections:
GND: C1.2, J1.2, R3.2, U1.2
unnamed: C1.1, J1.1, U1.5
unnamed: J1.3, R1.2, U1.4
unnamed: J1.4, R1.1, U1.3
unnamed: J1.5, R2.1, U1.1
unnamed: R2.2, R3.1

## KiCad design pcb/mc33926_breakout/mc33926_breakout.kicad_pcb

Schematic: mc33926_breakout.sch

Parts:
C1, C2: 0.47uF
C3, C4, C5, C6: 47uF
C7, C8: 33nF
C9: 0.1uF
D1: ZENER
Q1: MOSFET_N
R1, R2, R3, R4, R5, R6, R7, R10, R11, R12, R13, R14, R16, R18, R19: 1k
R8, R9: 220
R15, R17: 10k
R20: 100k
U1: MC33926_Conn
U2, U3: MC33926_IC

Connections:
ENP: R10.2, U2.9 (NC), U2.10 (EN), U3.9 (NC), U3.10 (EN)
FGND: C3.2, C4.2, C5.2, C6.2, D1.1, Q1.1, Q1.2, Q1.3, U2.5 (AGND), U2.17 (NC), U2.18 (PGND), U2.19 (PGND), U2.20 (PGND), U2.22 (PGND), U2.23 (PGND), U2.24 (PGND), U2.25 (NC), U2.33 (PAD), U3.5 (AGND), U3.17 (NC), U3.18 (PGND), U3.19 (PGND), U3.20 (PGND), U3.22 (PGND), U3.23 (PGND), U3.24 (PGND), U3.25 (NC), U3.33 (PAD)
GND: C1.2, C2.2, C9.1, Q1.5, Q1.6, Q1.7, Q1.8, R8.2, R9.2, U1.2 (GND), U1.21 (GND)
INVP: R12.2, U2.7 (INV), U3.7 (INV)
M1OUT1: U1.19 (M1OUT1), U2.12 (OUT1), U2.13 (OUT1), U2.14 (OUT1), U2.15 (OUT1)
M1OUT2: U1.20 (M1OUT2), U2.27 (OUT2), U2.28 (OUT2), U2.29 (OUT2), U2.30 (OUT2)
M2OUT1: U1.23 (M2OUT1), U3.12 (OUT1), U3.13 (OUT1), U3.14 (OUT1), U3.15 (OUT1)
M2OUT2: U1.24 (M2OUT2), U3.27 (OUT2), U3.28 (OUT2), U3.29 (OUT2), U3.30 (OUT2)
unnamed: C1.1, R4.1, U1.9 (M1FB)
unnamed: C2.1, R5.1, U1.18 (M2_FB)
unnamed: C7.2, U2.32 (CCP)
unnamed: C8.2, U3.32 (CCP)
unnamed: D1.2, Q1.4, R20.1
unnamed: R1.1, U1.7 (M1D1)
unnamed: R1.2, U2.26 (D1)
unnamed: R2.1, U1.16 (M2D1)
unnamed: R2.2, U3.26 (D1)
unnamed: R3.1, U1.11 (SLEW)
unnamed: R4.2, R8.1, U2.8 (FB)
unnamed: R5.2, R9.1, U3.8 (FB)
unnamed: R6.1, U1.5 (M1IN1)
unnamed: R6.2, U2.2 (IN1)
unnamed: R7.1, U1.14 (M2IN1)
unnamed: R7.2, U3.2 (IN1)
unnamed: R10.1, U1.10 (EN)
unnamed: R11.1, U1.8 (M1nSF)
unnamed: R11.2, R15.1, U2.21 (nSF)
unnamed: R12.1, U1.12 (INV)
unnamed: R13.1, U1.17 (M2nSF)
unnamed: R13.2, R17.1, U3.21 (nSF)
unnamed: R14.1, U1.6 (M1nD2)
unnamed: R14.2, U2.16 (nD2)
unnamed: R16.1, U1.4 (M1IN2)
unnamed: R16.2, U2.1 (IN2)
unnamed: R18.1, U1.13 (M2IN2)
unnamed: R18.2, U3.1 (IN2)
unnamed: R19.1, U1.15 (M2nD2)
unnamed: R19.2, U3.16 (nD2)
SLEWP: R3.2, U2.3 (SLEW), U3.3 (SLEW)
VIN: C3.1, C4.1, C5.1, C6.1, C7.1, C8.1, C9.2, R20.2, U1.1 (VIN), U1.22 (VIN), U2.4 (VPWR), U2.6 (VPWR), U2.11 (VPWR), U2.31 (VPWR), U3.4 (VPWR), U3.6 (VPWR), U3.11 (VPWR), U3.31 (VPWR)
Vdd: R15.2, R17.2, U1.3 (Vdd)

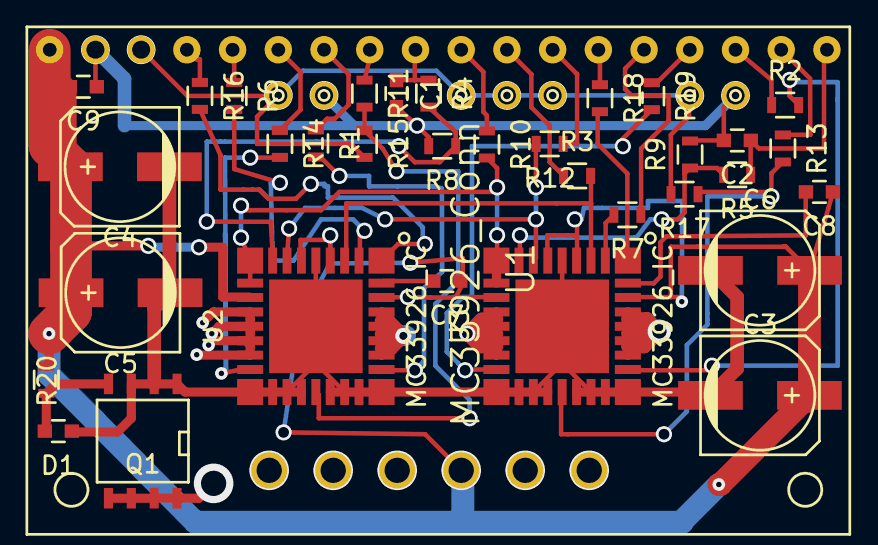
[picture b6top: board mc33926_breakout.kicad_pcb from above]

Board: 4 copper layers, 34 parts (0 on the bottom side), 41 nets.

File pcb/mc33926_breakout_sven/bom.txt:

C1, C2  - 0.47uF 10V  0603  	Farnell MC0603X474K100CT   
C3,C4,C5,C6   - 47uF 35V   6.3x5.8  Mouser EEE-FK1V470AP  
C7,C8  - 33nF  50V 0603   Farnell MC0603B333K500CT  
C9  - 0.1uF 35V  0603    Farnell CGA2B3X7R1V104K050BB  
D1  - Zener 30V  0603    Mouser 652-CD0603-Z30
Q1  - MOSFET N-Channel 30V  SO8   Mouser 78-SI4010DY-T1-GE3    
R1,R2,R3,R4,R5,R6,R7,R10,R11,R12,R13,R14,R16,R18,R19 -  1k 5% 0603 
R8,R9  - 220 5%   0603
R15,R17 - 10k  5% 0603
R20 - 100k  5%  0603
U2,U3 - Freescale MC33926PNB  QFN-EP 32
